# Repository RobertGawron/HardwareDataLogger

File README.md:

# HardwareDataLogger

## Summary

**_tl;dr it can collect, display, and store data locally and remotely, interfacing with various other devices._**

Modular, low-cost hardware data logger that can be easily extended or modified by changing the cards connected to it. The idea is that instead of reworking or changing the entire concept, only some cards need to be replaced, making it more reusable.

The project is based on:

* **STM32F103RBTx:** The main component, responsible for data processing.
* **ESP32-WROOM-32E:** For sending data to external nodes (e.g., Raspberry Pi).
* Software on a **remote node (Raspberry Pi):** Stores the data, processes it further, and provides a web interface with measurements for the user.

The project has the following features:

* **Pulse counting** from up to four devices (e.g., Geiger counters) with logic levels from 3.3V to 16V, using SMA connectors.
* **Data acquisition from measurement devices via UART**, utilizing a DB9 connector.
* User interface with a ***128x160 RGB LCD, four navigation buttons*** (up/down/left/right), and automatic LCD dimming in low light.
* UART over USB for transferring logged data to an external PC.
* ***microSD*** card for permanent data storage.
* ***WiFi*** capability for remote data transfer.

## Software

#### STM32F103RBTx Board
The STM32F103RBTx serves as the main microcontroller, handling data acquisition, processing, serialization, and user interaction.

* Toolchain: C++23, CubeMX, CMake.
* [More info.](./Software/STM32F103RBTx/README.md)

#### ESP32WROOM32E
The ESP32WROOM32E is only used for data transfer via WiFi; in the future, it will support FOTA (Firmware Over-The-Air).

* Toolchain: Rust.
* [More info.](./Software/ESP32WROOM32E/README.md)

## Hardware

Due to the availability of low-cost, high-quality PCB manufacturing, home-etched PCBs have become largely obsolete. While the PCB design for this project may be difficult to etch at home, it is still possible. [Subparts of the circuit can be assembled on a breadboard, making the process much easier](./Documentation/Pictures/Device_30_08_2021.jpg), and the modular software design allows for easy reuse of these components.

* Toolchain: KiCad
* Circuit exported to .pdf is available here (there are many PCBs due to modular design):
  
    * [DataAcquisitionUnit](./Hardware/DataAcquisitionUnit/README.md)
    * [DataProcessingUnit](./Hardware/DataProcessingUnit/README.md)
    * [HumanMachineInterface](./Hardware/HumanMachineInterface/README.md)
    * [MainBoard](./Hardware/MainBoard/README.md)
    * [ProcessingAndStorage](./Hardware/ProcessingAndStorage/README.md)

## Simulation

Embedded development is cool, but constantly flashing the target device for non-hardware-related logic, like the human-machine interface, can be time-consuming and frustrating. To make this easier, a simulation was developed that isolates the firmware not directly tied to hardware, adds stubs for drivers, and includes a GUI. This allows all high-level aspects, such as what’s displayed on the LCD, user interaction via buttons, and data parsing, to be tested without the need for hardware.

While this simulation handles the firmware, speed of execution isn't a concern since it focuses solely on high-level logic. For hardware or driver-related issues, traditional methods like using an oscilloscope or logic analyzer are still necessary, as the simulation cannot be used.

* Toolchain: Python (FastAPI), TypeScript.
* [More info.](./FirmwarePCSimulator/README.md)

## Integration Tests (Software in the Loop)

Unit tests are good (they are used in this project as well, along with code coverage), but they don't test the software as a whole. This is especially important here where there are multiple nodes (STM32, ESP8266, remote host). To fill this gap, fully automated integration tests were added.

* Toolchain: pytest, cmake.
* [More info.](./IntegrationTest/README.md)

## DevOps

It's good to let the machine handle the boring work of checking code quality.

* Toolchain: Unit tests (Google Test, Google Mock), code coverage (LCOV), static code analysis (CodeChecker), Docker (for both local development and CI), GitHub Actions (CI).

[Info on how to build the image and use the environment for development](./DevOps/README.md). Note that Simulation and Integration Tests (see below) have their own READMEs explaining usage, but they still use the common Docker image.

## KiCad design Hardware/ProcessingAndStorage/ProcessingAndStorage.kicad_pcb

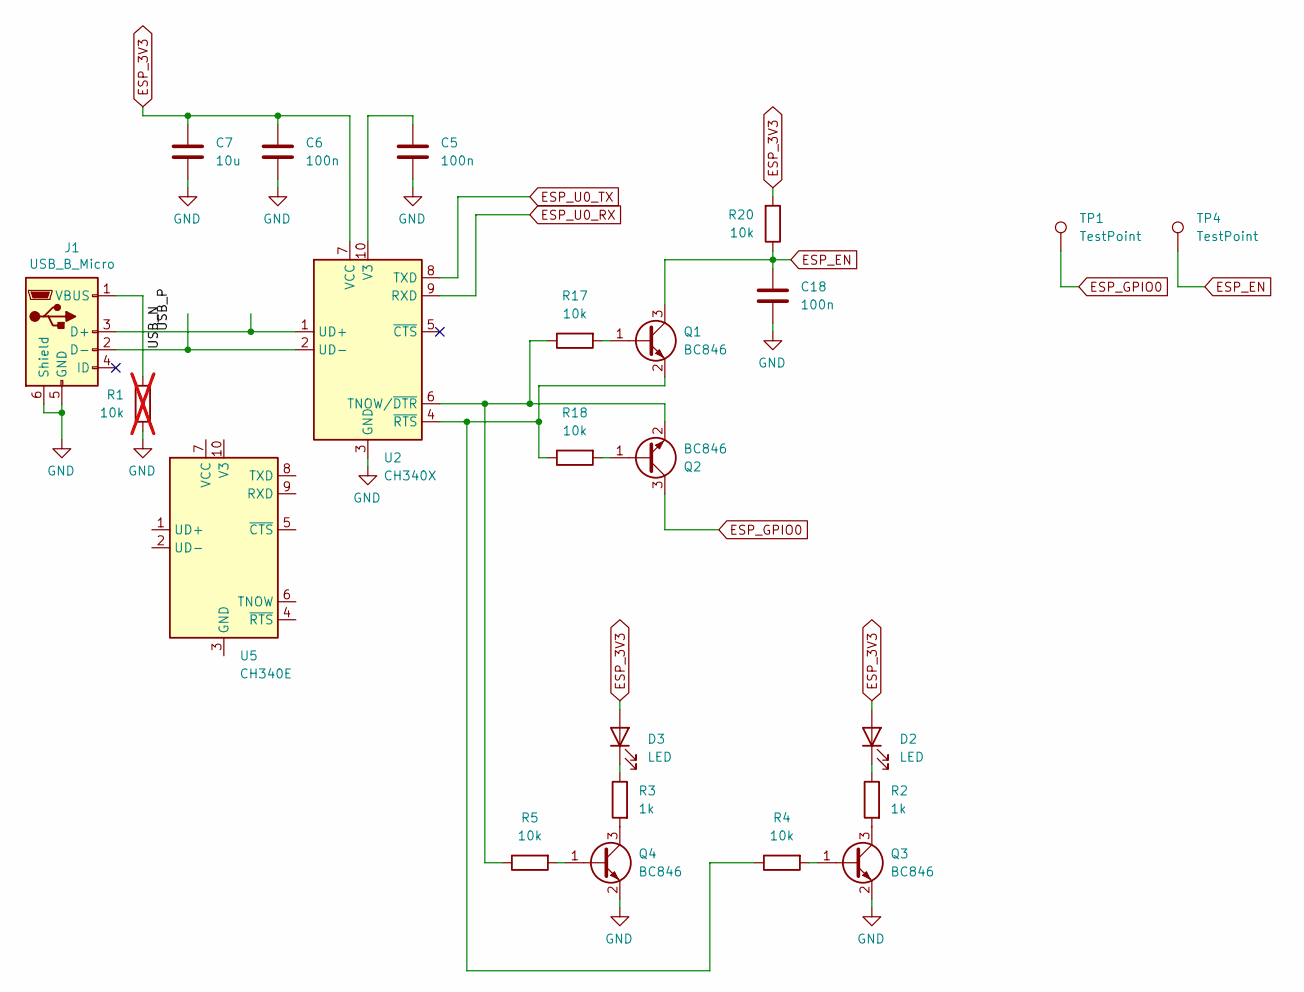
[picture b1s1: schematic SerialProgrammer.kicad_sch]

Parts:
C5, C6, C18: 100n; C_0805_2012Metric
C7: 10u; C_0805_2012Metric
D2, D3: LED; LED_0402_1005Metric
J1: USB_B_Micro; USB_Micro-B_Molex-105017-0001_Extra_Mechanical_Pads
Q1, Q2, Q3, Q4: BC846; SOT-23
R1: 10k; R_0805_2012Metric; not fitted
R2, R3: 1k; R_0805_2012Metric
R4, R5, R17, R18, R20: 10k; R_0805_2012Metric
TP1, TP4: TestPoint; TestPoint_Pad_D1.5mm
U2: CH340X; MSOP-10_3x3mm_P0.5mm
U5: CH340E; MSOP-10_3x3mm_P0.5mm

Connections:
/SerialProgrammer/USB_N: J1.2 (D-), U2.2 (UD-)
/SerialProgrammer/USB_P: J1.3 (D+), U2.1 (UD+)
ESP_3V3: C6.1, C7.1, D2.2 (A), D3.2 (A), R20.2, U2.7 (VCC); also elsewhere on the board
ESP_EN: C18.1, Q1.3 (C), R20.1, TP4.1; also elsewhere on the board
ESP_GPIO0: Q2.3 (C), TP1.1; also elsewhere on the board
ESP_U0_RX: U2.9 (RXD); also elsewhere on the board
ESP_U0_TX: U2.8 (TXD); also elsewhere on the board
GND: C5.2, C6.2, C7.2, C18.2, J1.5 (GND), J1.6 (Shield), Q3.2 (E), Q4.2 (E), R1.1, U2.3 (GND); also elsewhere on the board
unnamed: D2.1 (K), R2.1
unnamed: D3.1 (K), R3.1
unnamed: J1.1 (VBUS), R1.2
unnamed: Q1.1 (B), R17.2
unnamed: Q1.2 (E), R4.1, R18.1, U2.4 (~RTS)
unnamed: Q2.1 (B), R18.2
unnamed: Q2.2 (E), R5.1, R17.1, U2.6 (TNOW/~DTR)
unnamed: Q3.1 (B), R4.2
unnamed: Q3.3 (C), R2.2
unnamed: Q4.1 (B), R5.2
unnamed: Q4.3 (C), R3.2
unnamed: C5.1, U2.10 (V3)

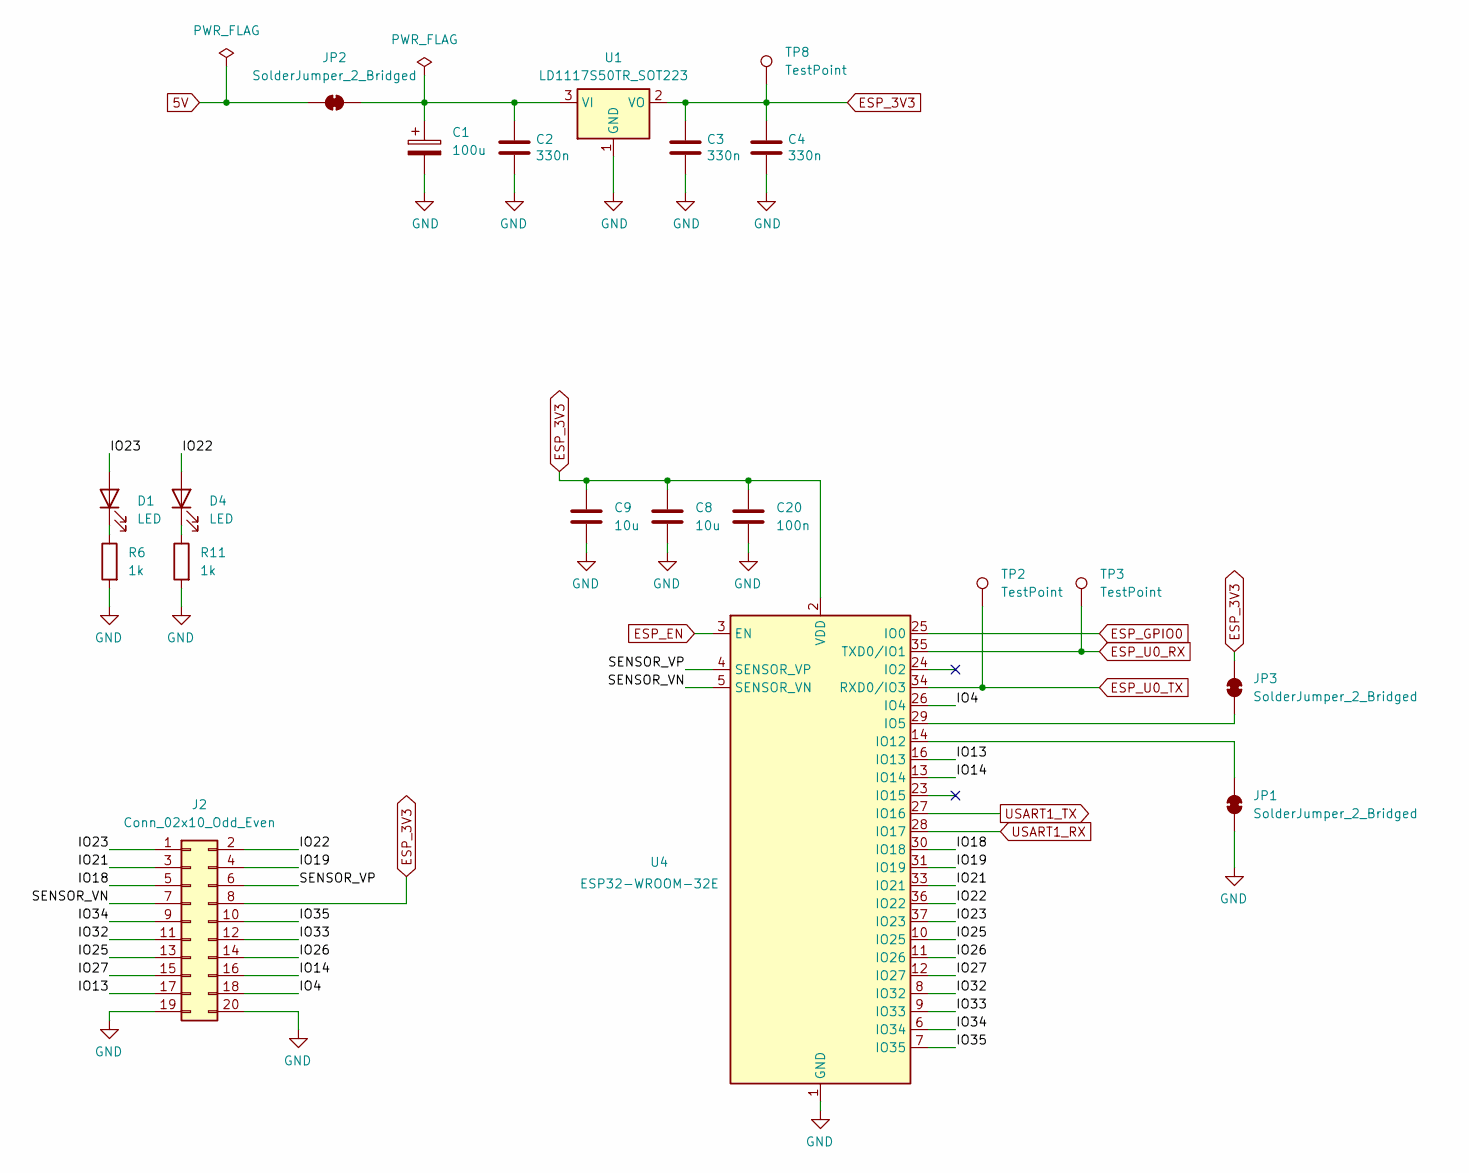
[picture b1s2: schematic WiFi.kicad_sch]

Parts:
C1: 100u; CP_Elec_6.3x5.8
C2, C3, C4: 330n; C_0805_2012Metric
C8, C9: 10u; C_0805_2012Metric
C20: 100n; C_0805_2012Metric
D1, D4: LED; LED_0402_1005Metric
J2: Conn_02x10_Odd_Even; PinHeader_2x10_P2.54mm_Horizontal
JP1, JP2, JP3: SolderJumper_2_Bridged; SolderJumper-2_P1.3mm_Bridged_Pad1.0x1.5mm
R6, R11: 1k; R_0805_2012Metric
TP2, TP3, TP8: TestPoint; TestPoint_Pad_D1.5mm
U1: LD1117S50TR_SOT223; SOT-223-3_TabPin2
U4: ESP32-WROOM-32E; ESP32-WROOM-32D

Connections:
5V: JP2.1 (A); also elsewhere on the board
/WiFi/IO4: J2.18, U4.26 (IO4)
/WiFi/IO13: J2.17, U4.16 (IO13)
/WiFi/IO14: J2.16, U4.13 (IO14)
/WiFi/IO18: J2.5, U4.30 (IO18)
/WiFi/IO19: J2.4, U4.31 (IO19)
/WiFi/IO21: J2.3, U4.33 (IO21)
/WiFi/IO22: D4.2 (A), J2.2, U4.36 (IO22)
/WiFi/IO23: D1.2 (A), J2.1, U4.37 (IO23)
/WiFi/IO25: J2.13, U4.10 (IO25)
/WiFi/IO26: J2.14, U4.11 (IO26)
/WiFi/IO27: J2.15, U4.12 (IO27)
/WiFi/IO32: J2.11, U4.8 (IO32)
/WiFi/IO33: J2.12, U4.9 (IO33)
/WiFi/IO34: J2.9, U4.6 (IO34)
/WiFi/IO35: J2.10, U4.7 (IO35)
/WiFi/SENSOR_VN: J2.7, U4.5 (SENSOR_VN)
/WiFi/SENSOR_VP: J2.6, U4.4 (SENSOR_VP)
ESP_3V3: C3.1, C4.1, C8.1, C9.1, C20.1, J2.8, JP3.2 (B), TP8.1, U1.2 (VO), U4.2 (VDD); also elsewhere on the board
ESP_EN: U4.3 (EN); also elsewhere on the board
ESP_GPIO0: U4.25 (IO0); also elsewhere on the board
ESP_U0_RX: TP3.1, U4.35 (TXD0/IO1); also elsewhere on the board
ESP_U0_TX: TP2.1, U4.34 (RXD0/IO3); also elsewhere on the board
GND: C1.2, C2.2, C3.2, C4.2, C8.2, C9.2, C20.2, J2.19, J2.20, JP1.1 (A), R6.2, R11.2, U1.1 (GND), U4.1 (GND), U4.15 (GND), U4.38 (GND), U4.39 (GND); also elsewhere on the board
unnamed: D1.1 (K), R6.1
unnamed: D4.1 (K), R11.1
unnamed: JP1.2 (B), U4.14 (IO12)
unnamed: C1.1, C2.1, JP2.2 (B), U1.3 (VI)
unnamed: JP3.1 (A), U4.29 (IO5)
USART1_RX: U4.28 (IO17); also elsewhere on the board
USART1_TX: U4.27 (IO16); also elsewhere on the board

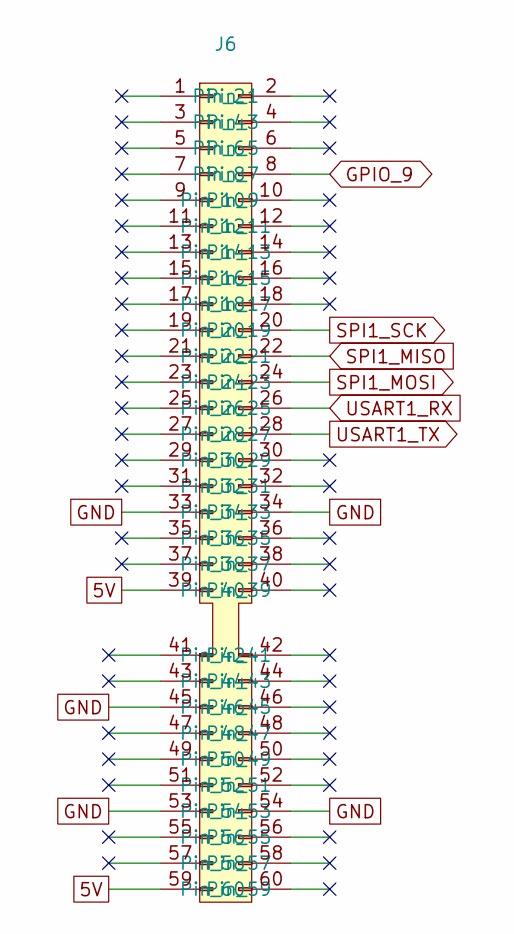
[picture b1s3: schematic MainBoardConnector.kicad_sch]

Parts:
J6: ExtensionConnector

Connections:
5V: J6.39, J6.59; also elsewhere on the board
GND: J6.33, J6.34, J6.45, J6.53, J6.54; also elsewhere on the board
GPIO_9: J6.8; also elsewhere on the board
SPI1_MISO: J6.22; also elsewhere on the board
SPI1_MOSI: J6.24; also elsewhere on the board
SPI1_SCK: J6.20; also elsewhere on the board
USART1_RX: J6.26; also elsewhere on the board
USART1_TX: J6.28; also elsewhere on the board

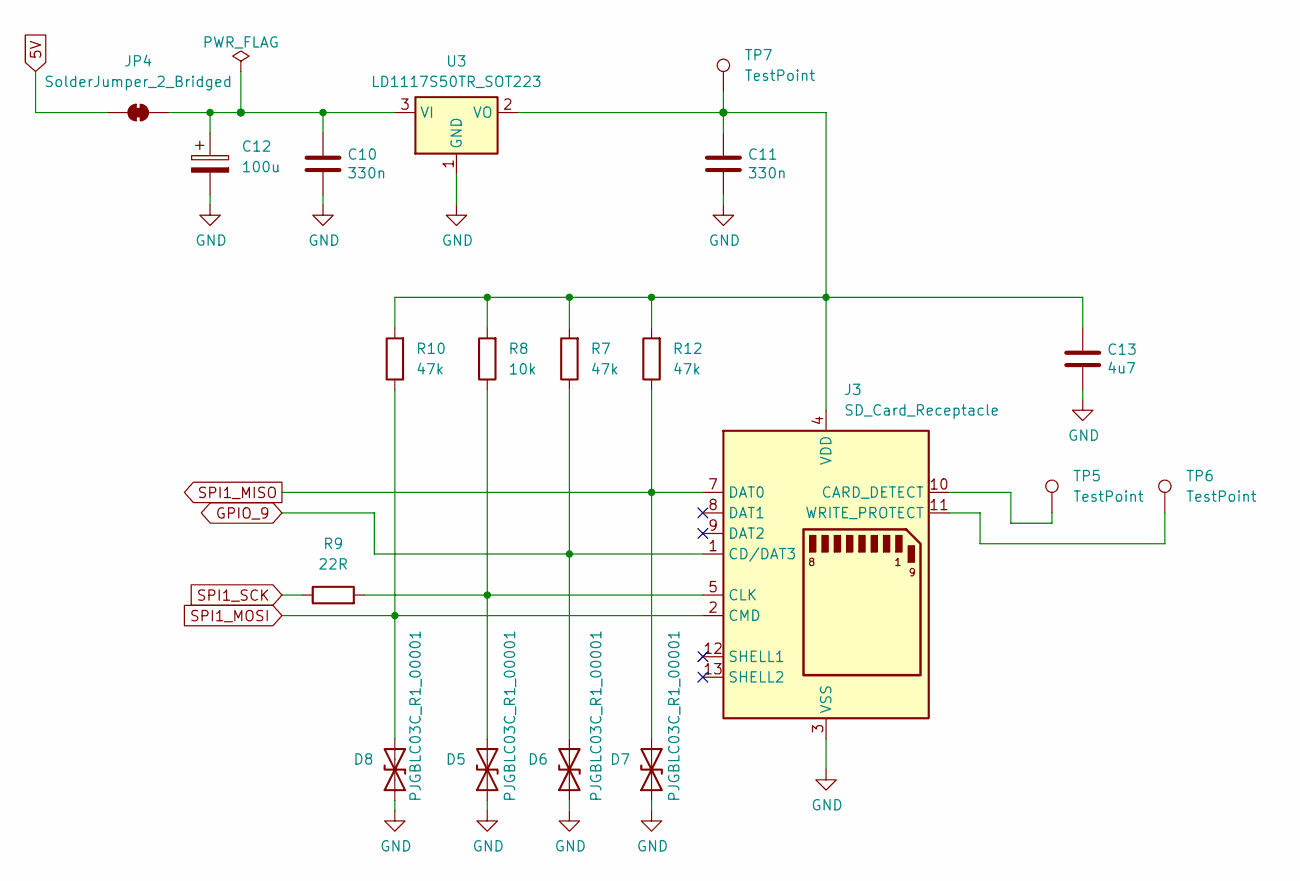
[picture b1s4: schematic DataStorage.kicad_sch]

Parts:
C10, C11: 330n; C_0805_2012Metric
C12: 100u; CP_Elec_6.3x5.8
C13: 4u7; C_0805_2012Metric
D5, D6, D7, D8: PJGBLC03C_R1_00001; D_SOD-323F
J3: SD_Card_Receptacle; SD_TE_2041021
JP4: SolderJumper_2_Bridged; SolderJumper-2_P1.3mm_Bridged_Pad1.0x1.5mm
R7, R10, R12: 47k; R_0805_2012Metric
R8: 10k; R_0805_2012Metric
R9: 22R; R_0805_2012Metric
TP5, TP6, TP7: TestPoint; TestPoint_Pad_D1.5mm
U3: LD1117S50TR_SOT223; SOT-223-3_TabPin2

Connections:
5V: JP4.1 (A); also elsewhere on the board
GND: C10.2, C11.2, C12.2, C13.2, D5.1 (A1), D6.1 (A1), D7.1 (A1), D8.1 (A1), J3.3 (VSS), J3.6 (VSS), U3.1 (GND); also elsewhere on the board
GPIO_9: D6.2 (A2), J3.1 (CD/DAT3), R7.1; also elsewhere on the board
unnamed: D5.2 (A2), J3.5 (CLK), R8.1, R9.2
unnamed: J3.10 (CARD_DETECT), TP5.1
unnamed: C11.1, C13.1, J3.4 (VDD), R7.2, R8.2, R10.2, R12.2, TP7.1, U3.2 (VO)
unnamed: J3.11 (WRITE_PROTECT), TP6.1
unnamed: C10.1, C12.1, JP4.2 (B), U3.3 (VI)
SPI1_MISO: D7.2 (A2), J3.7 (DAT0), R12.1; also elsewhere on the board
SPI1_MOSI: D8.2 (A2), J3.2 (CMD), R10.1; also elsewhere on the board
SPI1_SCK: R9.1; also elsewhere on the board

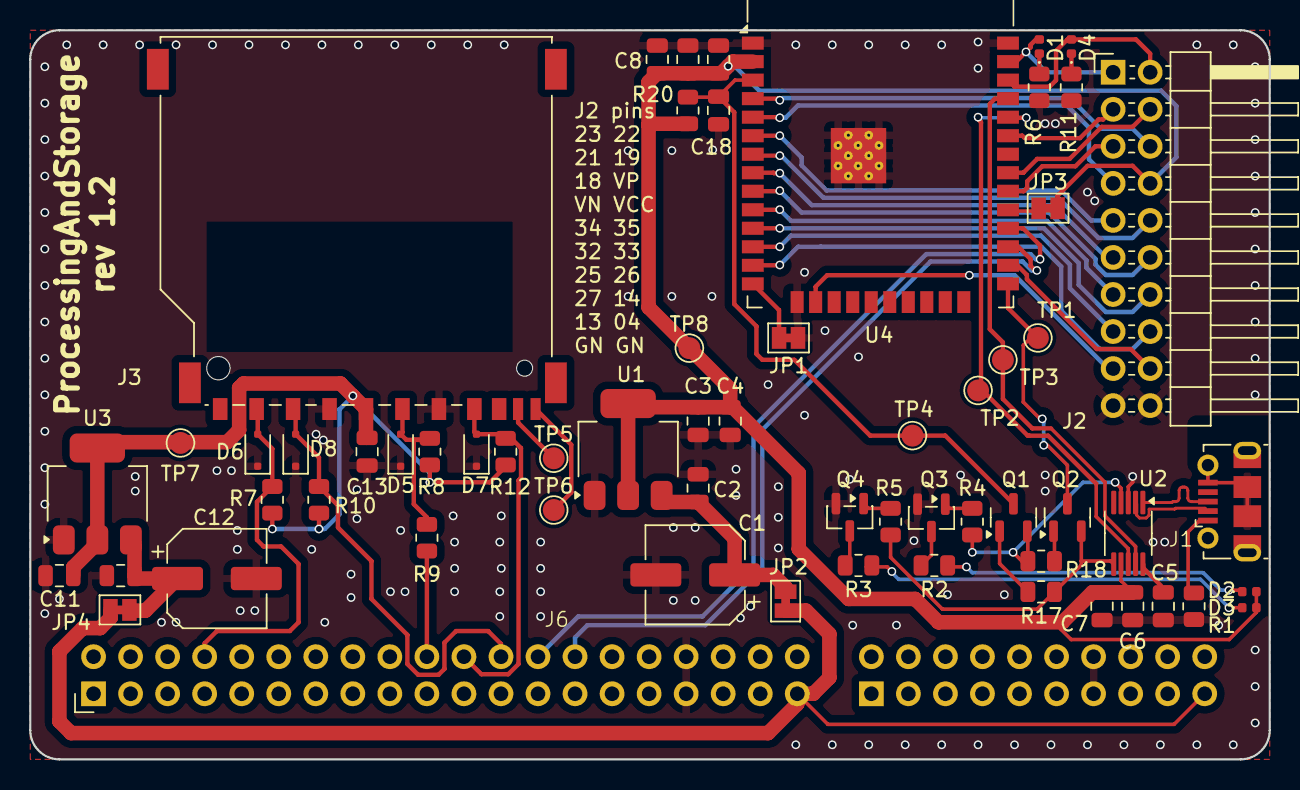
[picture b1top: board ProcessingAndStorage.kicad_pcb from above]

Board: 2 copper layers, 85.0 x 50.0 mm, 62 parts (0 on the bottom side), 54 nets.

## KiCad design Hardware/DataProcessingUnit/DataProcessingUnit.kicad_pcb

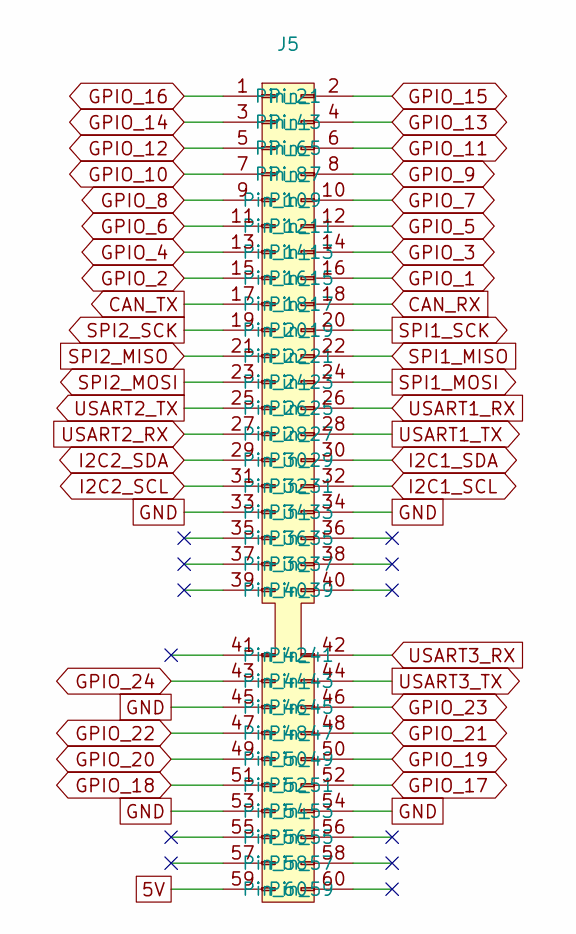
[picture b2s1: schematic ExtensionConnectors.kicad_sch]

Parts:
J5: ExtensionConnector

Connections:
5V: J5.59; also elsewhere on the board
CAN_RX: J5.18; also elsewhere on the board
CAN_TX: J5.17; also elsewhere on the board
GND: J5.33, J5.34, J5.45, J5.53, J5.54; also elsewhere on the board
GPIO_1: J5.16; also elsewhere on the board
GPIO_2: J5.15; also elsewhere on the board
GPIO_3: J5.14; also elsewhere on the board
GPIO_4: J5.13; also elsewhere on the board
GPIO_5: J5.12; also elsewhere on the board
GPIO_6: J5.11; also elsewhere on the board
GPIO_7: J5.10; also elsewhere on the board
GPIO_8: J5.9; also elsewhere on the board
GPIO_9: J5.8; also elsewhere on the board
GPIO_10: J5.7; also elsewhere on the board
GPIO_11: J5.6; also elsewhere on the board
GPIO_12: J5.5; also elsewhere on the board
GPIO_13: J5.4; also elsewhere on the board
GPIO_14: J5.3; also elsewhere on the board
GPIO_15: J5.2; also elsewhere on the board
GPIO_16: J5.1; also elsewhere on the board
GPIO_17: J5.52; also elsewhere on the board
GPIO_18: J5.51; also elsewhere on the board
GPIO_19: J5.50; also elsewhere on the board
GPIO_20: J5.49; also elsewhere on the board
GPIO_21: J5.48; also elsewhere on the board
GPIO_22: J5.47; also elsewhere on the board
GPIO_23: J5.46; also elsewhere on the board
GPIO_24: J5.43; also elsewhere on the board
I2C1_SCL: J5.32; also elsewhere on the board
I2C1_SDA: J5.30; also elsewhere on the board
I2C2_SCL: J5.31; also elsewhere on the board
I2C2_SDA: J5.29; also elsewhere on the board
SPI1_MISO: J5.22; also elsewhere on the board
SPI1_MOSI: J5.24; also elsewhere on the board
SPI1_SCK: J5.20; also elsewhere on the board
SPI2_MISO: J5.21; also elsewhere on the board
SPI2_MOSI: J5.23; also elsewhere on the board
SPI2_SCK: J5.19; also elsewhere on the board
USART1_RX: J5.26; also elsewhere on the board
USART1_TX: J5.28; also elsewhere on the board
USART2_RX: J5.27; also elsewhere on the board
USART2_TX: J5.25; also elsewhere on the board
USART3_RX: J5.42; also elsewhere on the board
USART3_TX: J5.44; also elsewhere on the board

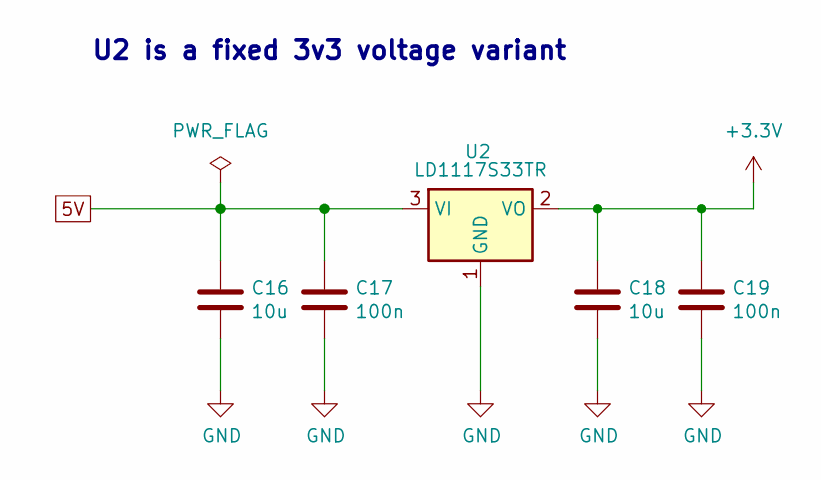
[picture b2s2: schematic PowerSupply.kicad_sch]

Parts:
C16, C18: 10u; C_0805_2012Metric
C17, C19: 100n; C_0805_2012Metric
U2: LD1117S33TR; SOT-223

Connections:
5V: C16.1, C17.1, U2.3 (VI); also elsewhere on the board
+3.3V: C18.1, C19.1, U2.2 (VO); also elsewhere on the board
GND: C16.2, C17.2, C18.2, C19.2, U2.1 (GND); also elsewhere on the board

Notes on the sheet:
U2 is a fixed 3v3 voltage variant

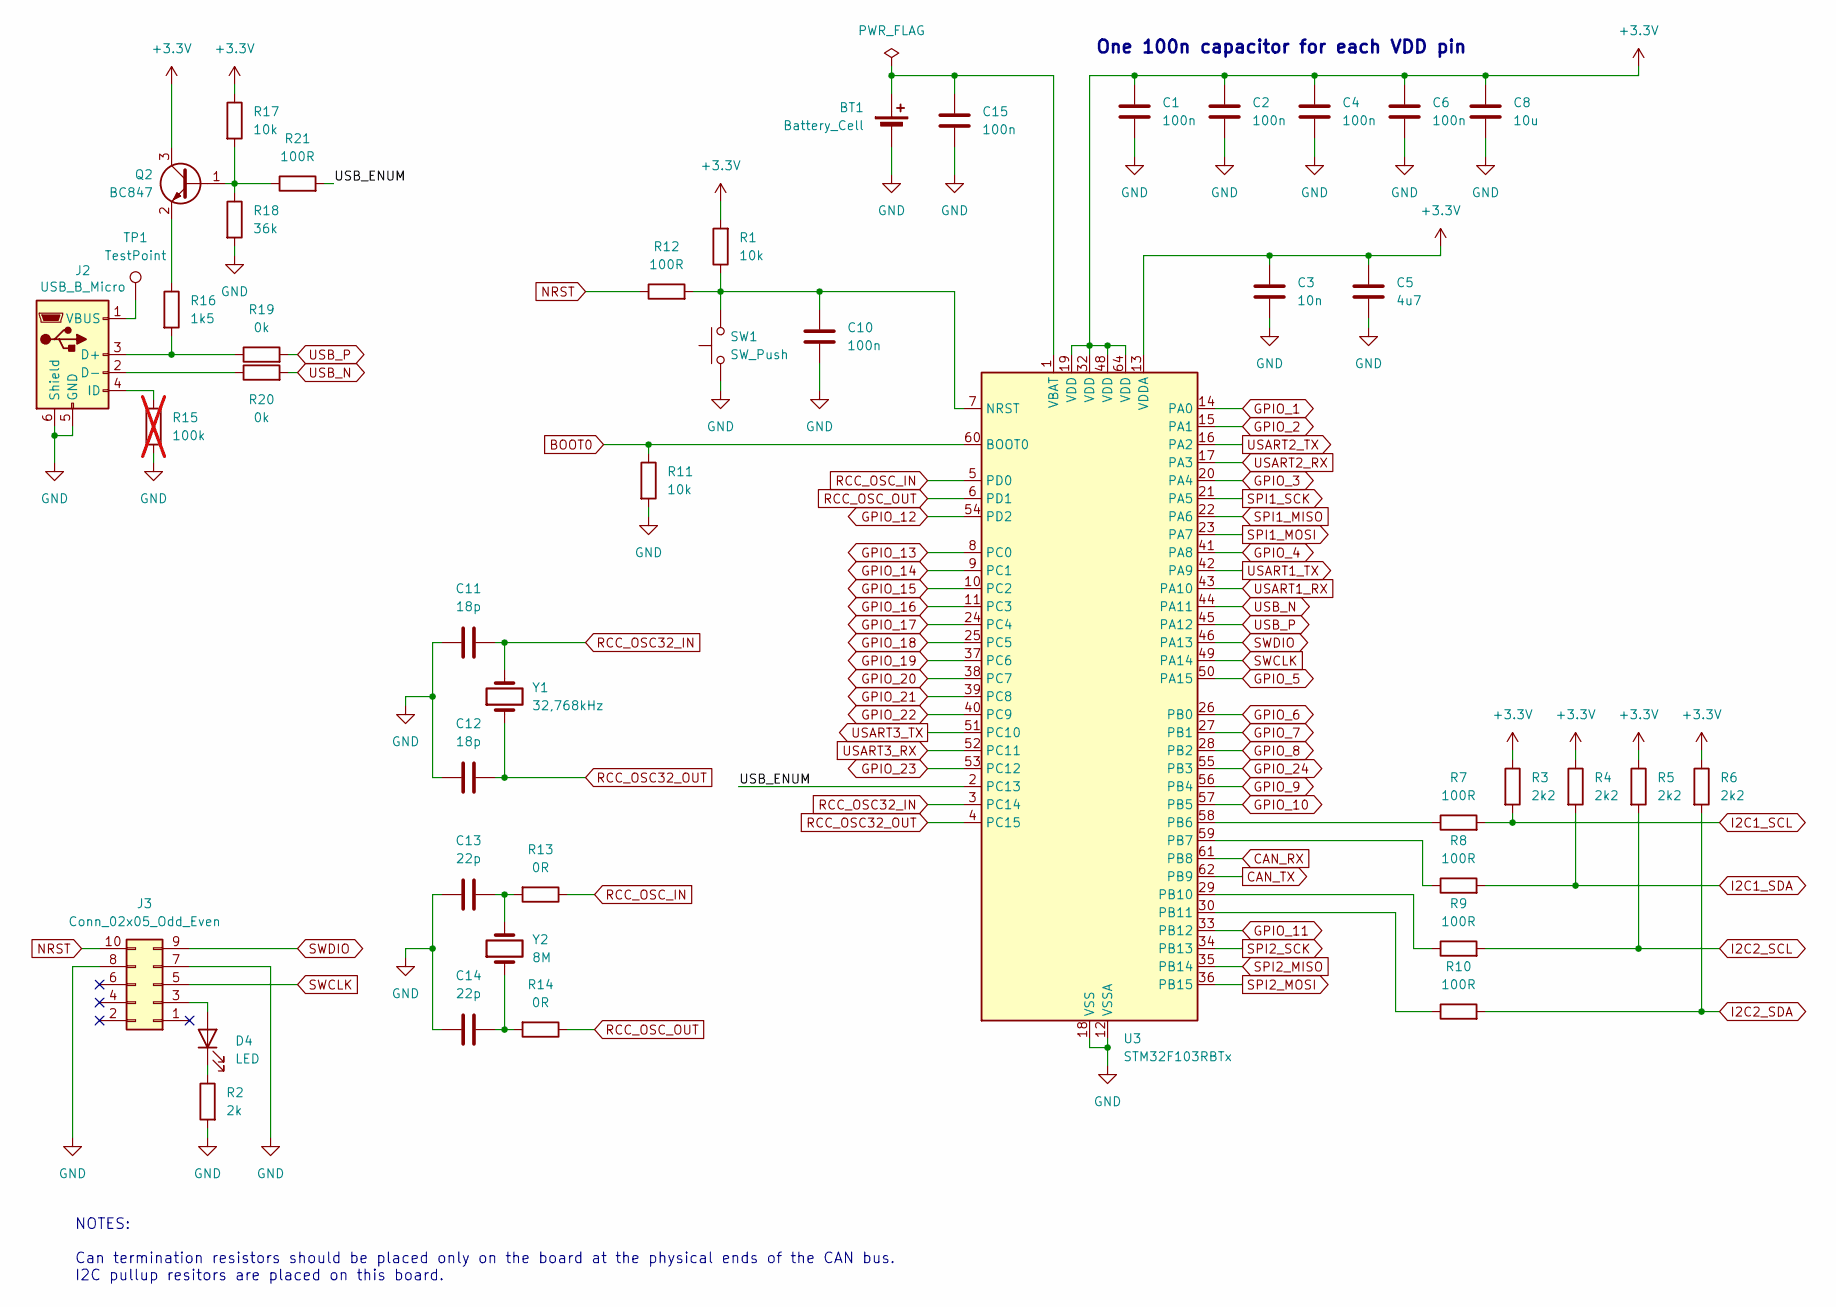
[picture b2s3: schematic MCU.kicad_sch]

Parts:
BT1: Battery_Cell; BatteryHolder_Keystone_1060_1x2032
C1, C2, C4, C6, C10, C15: 100n; C_0805_2012Metric
C3: 10n; C_0805_2012Metric
C5: 4u7; C_0805_2012Metric
C8: 10u; C_0805_2012Metric
C11, C12: 18p; C_0805_2012Metric
C13, C14: 22p; C_0805_2012Metric
D4: LED; LED_0402_1005Metric
J2: USB_B_Micro; USB_Micro-B_Molex-105017-0001_Extra_Mechanical_Pads
J3: Conn_02x05_Odd_Even; PinSocket_2x05_P2.00mm_Horizontal
Q2: BC847; SOT-23
R1, R11, R17: 10k; R_0805_2012Metric
R2: 2k; R_0805_2012Metric
R3, R4, R5, R6: 2k2; R_0805_2012Metric
R7, R8, R9, R10, R12, R21: 100R; R_0805_2012Metric
R13, R14: 0R; R_0805_2012Metric
R15: 100k; R_0805_2012Metric; not fitted
R16: 1k5; R_0805_2012Metric
R18: 36k; R_0805_2012Metric
R19, R20: 0k; R_0805_2012Metric
SW1: SW_Push; SW_SPST_EVPBF
TP1: TestPoint; TestPoint_Pad_D1.5mm
U3: STM32F103RBTx; LQFP-64_10x10mm_P0.5mm
Y1: 32,768kHz; Crystal_SMD_3215-2Pin_3.2x1.5mm
Y2: 8M; Crystal_SMD_HC49-SD

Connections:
+3.3V: C1.1, C2.1, C3.1, C4.1, C5.1, C6.1, C8.1, Q2.3 (C), R1.2, R3.1, R4.1, R5.1, R6.1, R17.1, U3.13 (VDDA), U3.19 (VDD), U3.32 (VDD), U3.48 (VDD), U3.64 (VDD); also elsewhere on the board
/MCU/USB_ENUM: R21.2, U3.2 (PC13)
BOOT0: R11.1, U3.60 (BOOT0)
CAN_RX: U3.61 (PB8); also elsewhere on the board
CAN_TX: U3.62 (PB9); also elsewhere on the board
GND: BT1.2 (-), C1.2, C2.2, C3.2, C4.2, C5.2, C6.2, C8.2, C10.2, C11.1, C12.1, C13.1, C14.1, C15.2, J2.5 (GND), J2.6 (Shield), J3.7, J3.8, R2.2, R11.2, R15.2, R18.2, SW1.1, U3.12 (VSSA), U3.18 (VSS), U3.31 (VSS), U3.47 (VSS), U3.63 (VSS); also elsewhere on the board
GPIO_1: U3.14 (PA0); also elsewhere on the board
GPIO_2: U3.15 (PA1); also elsewhere on the board
GPIO_3: U3.20 (PA4); also elsewhere on the board
GPIO_4: U3.41 (PA8); also elsewhere on the board
GPIO_5: U3.50 (PA15); also elsewhere on the board
GPIO_6: U3.26 (PB0); also elsewhere on the board
GPIO_7: U3.27 (PB1); also elsewhere on the board
GPIO_8: U3.28 (PB2); also elsewhere on the board
GPIO_9: U3.56 (PB4); also elsewhere on the board
GPIO_10: U3.57 (PB5); also elsewhere on the board
GPIO_11: U3.33 (PB12); also elsewhere on the board
GPIO_12: U3.54 (PD2); also elsewhere on the board
GPIO_13: U3.8 (PC0); also elsewhere on the board
GPIO_14: U3.9 (PC1); also elsewhere on the board
GPIO_15: U3.10 (PC2); also elsewhere on the board
GPIO_16: U3.11 (PC3); also elsewhere on the board
GPIO_17: U3.24 (PC4); also elsewhere on the board
GPIO_18: U3.25 (PC5); also elsewhere on the board
GPIO_19: U3.37 (PC6); also elsewhere on the board
GPIO_20: U3.38 (PC7); also elsewhere on the board
GPIO_21: U3.39 (PC8); also elsewhere on the board
GPIO_22: U3.40 (PC9); also elsewhere on the board
GPIO_23: U3.53 (PC12); also elsewhere on the board
GPIO_24: U3.55 (PB3); also elsewhere on the board
I2C1_SCL: R3.2, R7.2; also elsewhere on the board
I2C1_SDA: R4.2, R8.2; also elsewhere on the board
I2C2_SCL: R5.2, R9.2; also elsewhere on the board
I2C2_SDA: R6.2, R10.2; also elsewhere on the board
NRST: J3.10, R12.1
unnamed: BT1.1 (+), C15.1, U3.1 (VBAT)
unnamed: C13.2, R13.2, Y2.2
unnamed: C14.2, R14.2, Y2.1
unnamed: D4.2 (A), J3.3
unnamed: D4.1 (K), R2.1
unnamed: J2.3 (D+), R16.2, R19.1
unnamed: J2.2 (D-), R20.1
unnamed: J2.4 (ID), R15.1
unnamed: J2.1 (VBUS), TP1.1
unnamed: Q2.1 (B), R17.2, R18.1, R21.1
unnamed: Q2.2 (E), R16.1
unnamed: C10.1, R1.1, R12.2, SW1.2, U3.7 (NRST)
unnamed: R7.1, U3.58 (PB6)
unnamed: R8.1, U3.59 (PB7)
unnamed: R9.1, U3.29 (PB10)
unnamed: R10.1, U3.30 (PB11)
RCC_OSC32_IN: C11.2, U3.3 (PC14), Y1.2
RCC_OSC32_OUT: C12.2, U3.4 (PC15), Y1.1
RCC_OSC_IN: R13.1, U3.5 (PD0)
RCC_OSC_OUT: R14.1, U3.6 (PD1)
SPI1_MISO: U3.22 (PA6); also elsewhere on the board
SPI1_MOSI: U3.23 (PA7); also elsewhere on the board
SPI1_SCK: U3.21 (PA5); also elsewhere on the board
SPI2_MISO: U3.35 (PB14); also elsewhere on the board
SPI2_MOSI: U3.36 (PB15); also elsewhere on the board
SPI2_SCK: U3.34 (PB13); also elsewhere on the board
SWCLK: J3.5, U3.49 (PA14)
SWDIO: J3.9, U3.46 (PA13)
USART1_RX: U3.43 (PA10); also elsewhere on the board
USART1_TX: U3.42 (PA9); also elsewhere on the board
USART2_RX: U3.17 (PA3); also elsewhere on the board
USART2_TX: U3.16 (PA2); also elsewhere on the board
USART3_RX: U3.52 (PC11); also elsewhere on the board
USART3_TX: U3.51 (PC10); also elsewhere on the board
USB_N: R20.2, U3.44 (PA11)
USB_P: R19.2, U3.45 (PA12)

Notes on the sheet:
One 100n capacitor for each VDD pin
NOTES: Can termination resistors should be placed only on the board at the physical ends of the CAN bus. I2C pullup resitors are placed on this board.

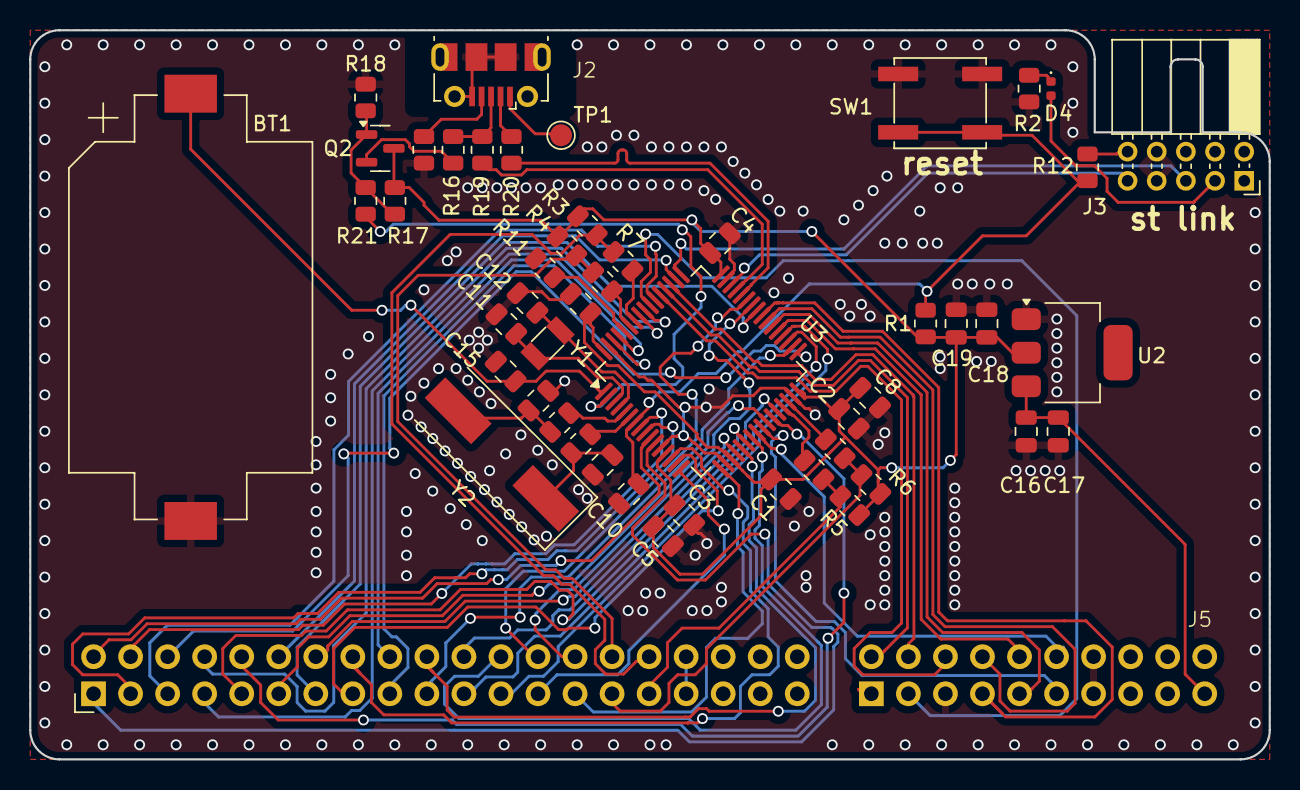
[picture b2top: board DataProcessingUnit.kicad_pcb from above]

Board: 2 copper layers, 85.0 x 50.0 mm, 50 parts (0 on the bottom side), 72 nets.

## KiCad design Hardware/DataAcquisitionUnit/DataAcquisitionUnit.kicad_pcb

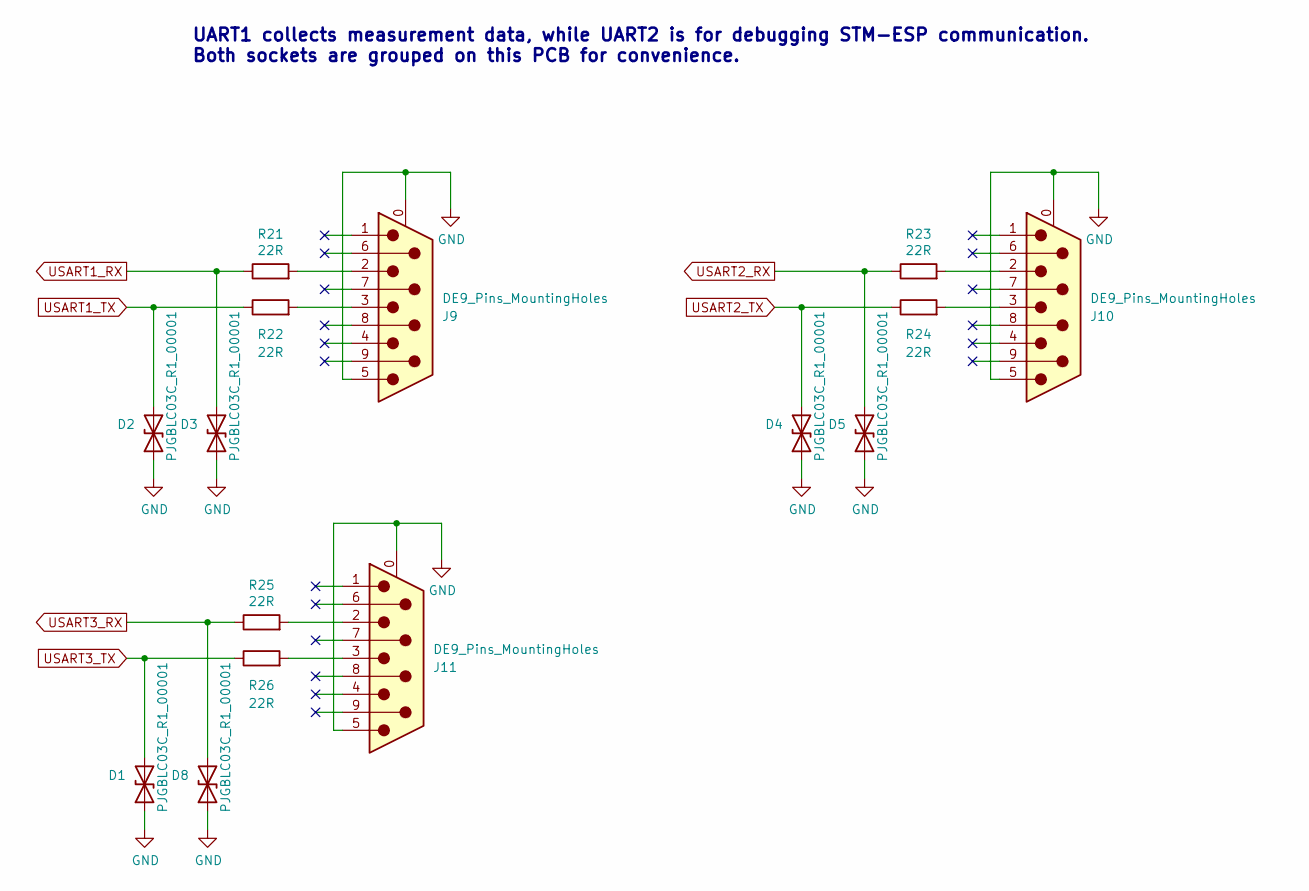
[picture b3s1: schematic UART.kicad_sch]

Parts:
D1, D2, D3, D4, D5, D8: PJGBLC03C_R1_00001; D_SOD-323F
J9, J10, J11: DE9_Pins_MountingHoles; DSUB-9_Socket_Vertical_P2.77x2.84mm_MountingHoles
R21, R22, R23, R24, R25, R26: 22R; R_0805_2012Metric

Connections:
GND: D1.1 (A1), D2.1 (A1), D3.1 (A1), D4.1 (A1), D5.1 (A1), D8.1 (A1), J9.0 (PAD), J9.5, J10.0 (PAD), J10.5, J11.0 (PAD), J11.5; also elsewhere on the board
unnamed: J9.2, R21.2
unnamed: J9.3, R22.2
unnamed: J10.2, R23.2
unnamed: J10.3, R24.2
unnamed: J11.2, R25.2
unnamed: J11.3, R26.2
USART1_RX: D3.2 (A2), R21.1; also elsewhere on the board
USART1_TX: D2.2 (A2), R22.1; also elsewhere on the board
USART2_RX: D5.2 (A2), R23.1; also elsewhere on the board
USART2_TX: D4.2 (A2), R24.1; also elsewhere on the board
USART3_RX: D8.2 (A2), R25.1; also elsewhere on the board
USART3_TX: D1.2 (A2), R26.1; also elsewhere on the board

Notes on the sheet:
UART1 collects measurement data, while UART2 is for debugging STM-ESP communication. Both sockets are grouped on this PCB for convenience.

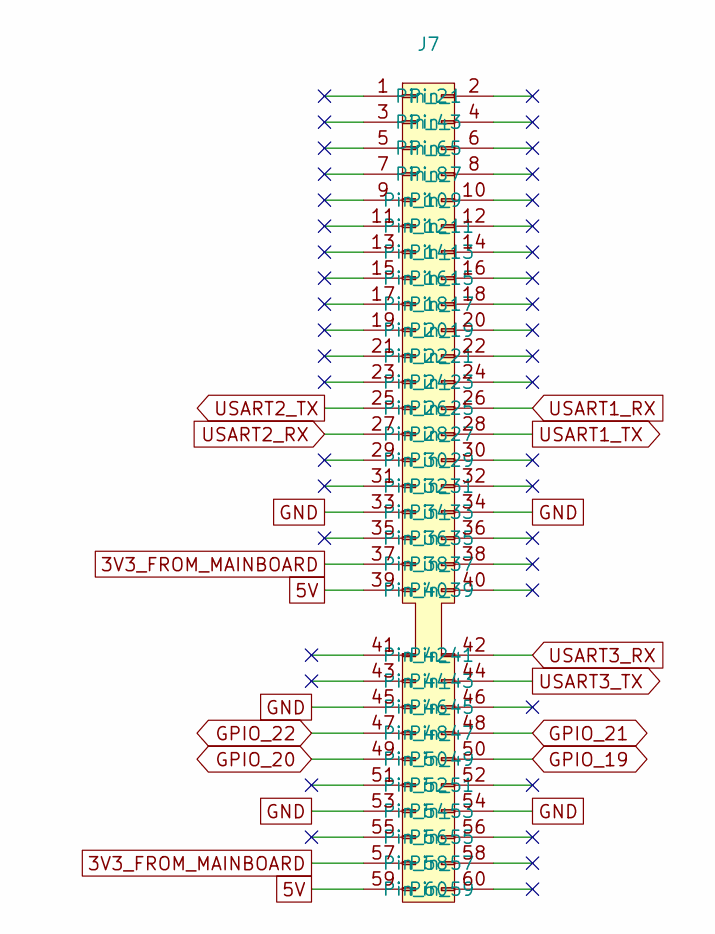
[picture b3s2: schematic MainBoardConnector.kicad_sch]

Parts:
J7: ExtensionConnector

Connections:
3V3_FROM_MAINBOARD: J7.37, J7.57; also elsewhere on the board
5V: J7.39, J7.59; also elsewhere on the board
GND: J7.33, J7.34, J7.45, J7.53, J7.54; also elsewhere on the board
GPIO_19: J7.50; also elsewhere on the board
GPIO_20: J7.49; also elsewhere on the board
GPIO_21: J7.48; also elsewhere on the board
GPIO_22: J7.47; also elsewhere on the board
USART1_RX: J7.26; also elsewhere on the board
USART1_TX: J7.28; also elsewhere on the board
USART2_RX: J7.27; also elsewhere on the board
USART2_TX: J7.25; also elsewhere on the board
USART3_RX: J7.42; also elsewhere on the board
USART3_TX: J7.44; also elsewhere on the board
